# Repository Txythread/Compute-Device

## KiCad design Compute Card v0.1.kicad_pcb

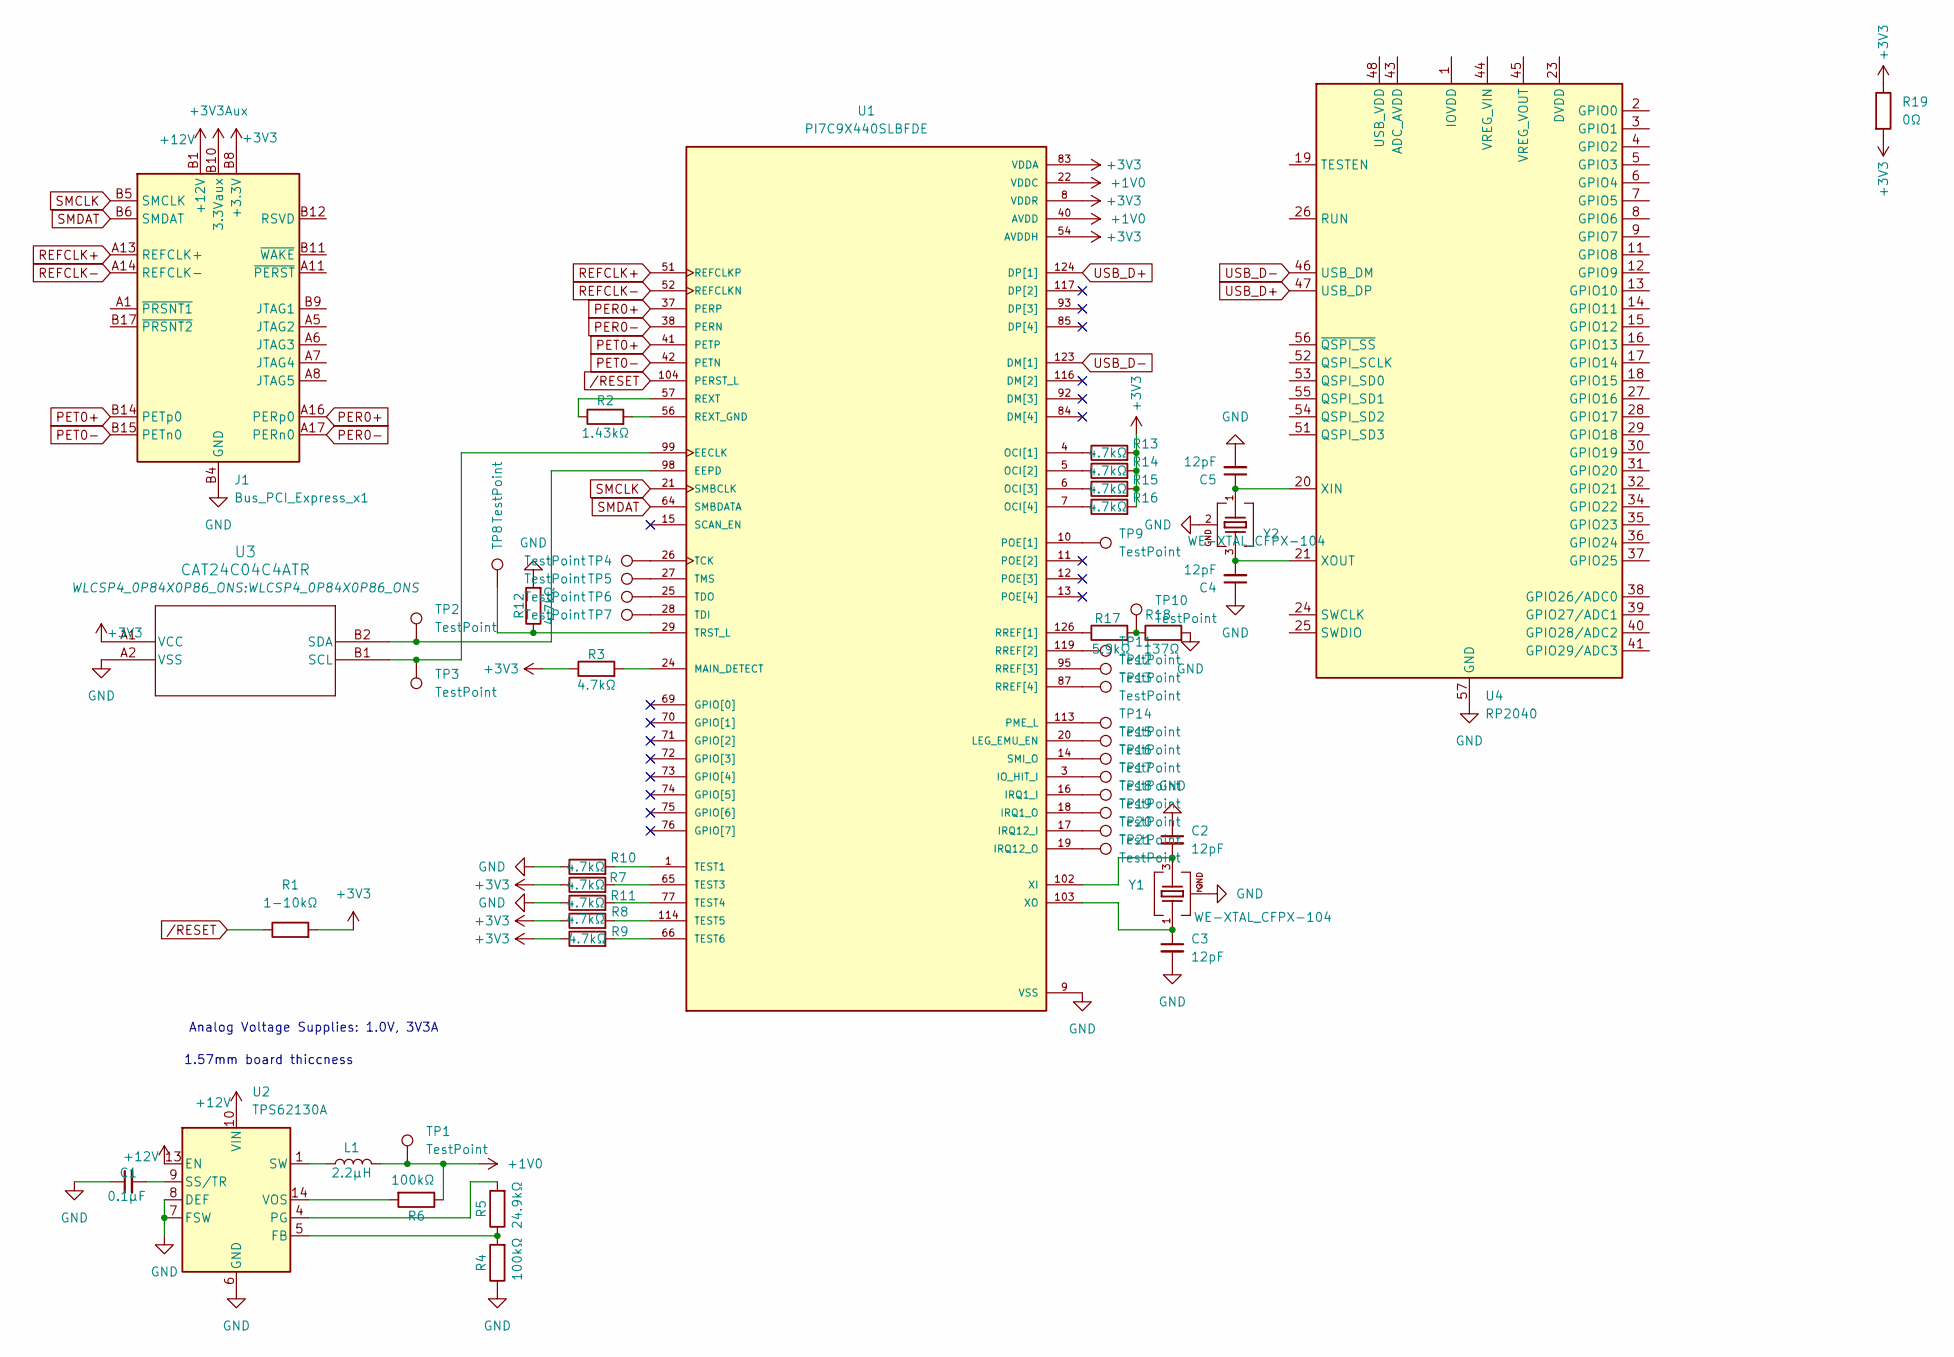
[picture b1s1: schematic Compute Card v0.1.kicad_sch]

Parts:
C1: 0.1µF; C_0805_2012Metric_Pad1.18x1.45mm_HandSolder
C2, C3, C4, C5: 12pF; C_0603_1608Metric
J1: Bus_PCI_Express_x1; BUS_PCIexpress_x1
L1: 2.2µH; L_0805_2012Metric_Pad1.05x1.20mm_HandSolder
R1: 1-10kΩ; R_0603_1608Metric_Pad0.98x0.95mm_HandSolder
R2: 1.43kΩ; R_0603_1608Metric_Pad0.98x0.95mm_HandSolder
R3, R7, R8, R9, R10, R11, R12, R13, R14, R15, R16: 4.7kΩ; R_0805_2012Metric_Pad1.20x1.40mm_HandSolder
R4, R6: 100kΩ; R_0805_2012Metric_Pad1.20x1.40mm_HandSolder
R5: 24.9kΩ; R_0805_2012Metric_Pad1.20x1.40mm_HandSolder
R17: 5.9kΩ; R_0603_1608Metric
R18: 137Ω; R_1206_3216Metric
R19: 0Ω; R_0805_2012Metric
TP1, TP2, TP3, TP4, TP5, TP6, TP7, TP8, TP9, TP10, TP11, TP12, TP13, TP14, TP15, TP16, TP17, TP18, TP19, TP20, TP21: TestPoint; TestPoint_Pad_D1.0mm
U1: PI7C9X440SLBFDE; QFP40P1600X1600X160-129N; PARTREV 3; DigiKey_Part_Number PI7C9X440SLBFDE-ND
U2: TPS62130A; VQFN-16-1EP_3x3mm_P0.5mm_EP1.68x1.68mm_ThermalVias
U3: CAT24C04C4ATR; WLCSP4_0P84X0P86_ONS
U4: RP2040; QFN-56-1EP_7x7mm_P0.4mm_EP3.2x3.2mm_ThermalVias
Y1, Y2: WE-XTAL_CFPX-104; DigiKey_Part_Number 1923-830059522CT-ND

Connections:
+1V0: L1.2, R6.1, TP1.1, U1.22 (VDDC), U1.35 (VDDC), U1.40 (AVDD), U1.46 (AVDD), U1.49 (AVDD), U1.60 (AVDD), U1.81 (VDDC), U1.100 (VDDC), U1.109 (VDDC), U1.111 (VDDC)
+3V3: J1.A9 (+3.3V), J1.A10 (+3.3V), J1.B8 (+3.3V), R1.2, R3.1, R7.1, R8.1, R9.1, R13.2, R14.2, R15.2, R16.2, R19.1, R19.2, U1.8 (VDDR), U1.33 (VDDR), U1.54 (AVDDH), U1.67 (VDDR), U1.83 (VDDA), U1.90 (VDDA), U1.91 (VDDA), U1.97 (VDDA), U1.105 (VDDR), U1.112 (VDDR), U1.115 (VDDA), U1.121 (VDDA), U1.122 (VDDA), U1.128 (VDDA), U3.A1 (VCC)
+3V3Aux: J1.B10 (3.3Vaux)
+12V: J1.A2 (+12V), J1.A3 (+12V), J1.B1 (+12V), J1.B2 (+12V), J1.B3 (+12V), U2.10 (VIN), U2.11 (VIN), U2.12 (VIN), U2.13 (EN)
GND: C1.1, C2.1, C3.2, C4.1, C5.2, J1.A4 (GND), J1.A12 (GND), J1.A15 (GND), J1.A18 (GND), J1.B4 (GND), J1.B7 (GND), J1.B13 (GND), J1.B16 (GND), J1.B18 (GND), R4.1, R10.1, R11.1, R12.2, R18.2, U1.9 (VSS), U1.23 (VSS), U1.34 (VSS), U1.36 (VSS), U1.39 (VSS), U1.45 (VSS), U1.50 (VSS), U1.53 (VSS), U1.61 (VSS), U1.68 (VSS), U1.82 (VSS), U1.86 (VSS), U1.89 (VSS), U1.94 (VSS), U1.96 (VSS), U1.101 (VSS), U1.106 (VSS), U1.110 (VSS), U1.118 (VSS), U1.120 (VSS), U1.125 (VSS), U1.127 (VSS), U1.129 (VSS), U2.6 (GND), U2.7 (FSW), U2.8 (DEF), U2.15 (GND), U2.16 (GND), U2.17 (GND), U3.A2 (VSS), U4.57 (GND), Y1.2, Y1.4, Y2.2, Y2.4
unnamed: L1.1, U2.1 (SW), U2.2 (SW), U2.3 (SW)
unnamed: R17.2, R18.1, TP10.1
unnamed: TP3.1, U1.99 (EECLK), U3.B1 (SCL)
unnamed: TP2.1, U1.98 (EEPD), U3.B2 (SDA)
unnamed: TP17.1, U1.3 (IO_HIT_I)
unnamed: TP18.1, U1.16 (IRQ1_I)
unnamed: TP19.1, U1.18 (IRQ1_O)
unnamed: TP20.1, U1.17 (IRQ12_I)
unnamed: TP21.1, U1.19 (IRQ12_O)
unnamed: TP15.1, U1.20 (LEG_EMU_EN)
unnamed: R3.2, U1.24 (MAIN_DETECT)
unnamed: R13.1, U1.4 (OCI[1])
unnamed: R14.1, U1.5 (OCI[2])
unnamed: R15.1, U1.6 (OCI[3])
unnamed: R16.1, U1.7 (OCI[4])
unnamed: TP14.1, U1.113 (PME_L)
unnamed: TP9.1, U1.10 (POE[1])
unnamed: R2.1, U1.57 (REXT)
unnamed: R2.2, U1.56 (REXT_GND)
unnamed: R17.1, U1.126 (RREF[1])
unnamed: TP11.1, U1.119 (RREF[2])
unnamed: TP12.1, U1.95 (RREF[3])
unnamed: TP13.1, U1.87 (RREF[4])
unnamed: TP16.1, U1.14 (SMI_O)
unnamed: TP4.1, U1.26 (TCK)
unnamed: TP7.1, U1.28 (TDI)
unnamed: TP6.1, U1.25 (TDO)
unnamed: R10.2, U1.1 (TEST1)
unnamed: R7.2, U1.65 (TEST3)
unnamed: R11.2, U1.77 (TEST4)
unnamed: R8.2, U1.114 (TEST5)
unnamed: R9.2, U1.66 (TEST6)
unnamed: TP5.1, U1.27 (TMS)
unnamed: R12.1, TP8.1, U1.29 (TRST_L)
unnamed: C2.2, U1.102 (XI), Y1.3
unnamed: C3.1, U1.103 (XO), Y1.1
unnamed: R4.2, R5.1, U2.5 (FB)
unnamed: R5.2, U2.4 (PG)
unnamed: C1.2, U2.9 (SS/TR)
unnamed: R6.2, U2.14 (VOS)
unnamed: U4.23 (DVDD), U4.50 (DVDD)
unnamed: U4.1 (IOVDD), U4.10 (IOVDD), U4.22 (IOVDD), U4.33 (IOVDD), U4.42 (IOVDD), U4.49 (IOVDD)
unnamed: C5.1, U4.20 (XIN), Y2.1
unnamed: C4.2, U4.21 (XOUT), Y2.3
PER0+: J1.A16 (PERp0), U1.37 (PERP)
PER0-: J1.A17 (PERn0), U1.38 (PERN)
PET0+: J1.B14 (PETp0), U1.41 (PETP)
PET0-: J1.B15 (PETn0), U1.42 (PETN)
REFCLK+: J1.A13 (REFCLK+), U1.51 (REFCLKP)
REFCLK-: J1.A14 (REFCLK-), U1.52 (REFCLKN)
SMCLK: J1.B5 (SMCLK), U1.21 (SMBCLK)
SMDAT: J1.B6 (SMDAT), U1.64 (SMBDATA)
USB_D+: U1.124 (DP[1]), U4.47 (USB_DP)
USB_D-: U1.123 (DM[1]), U4.46 (USB_DM)
/RESET: R1.1, U1.104 (PERST_L)

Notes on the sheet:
1.57mm board thiccness
Analog Voltage Supplies: 1.0V, 3V3A

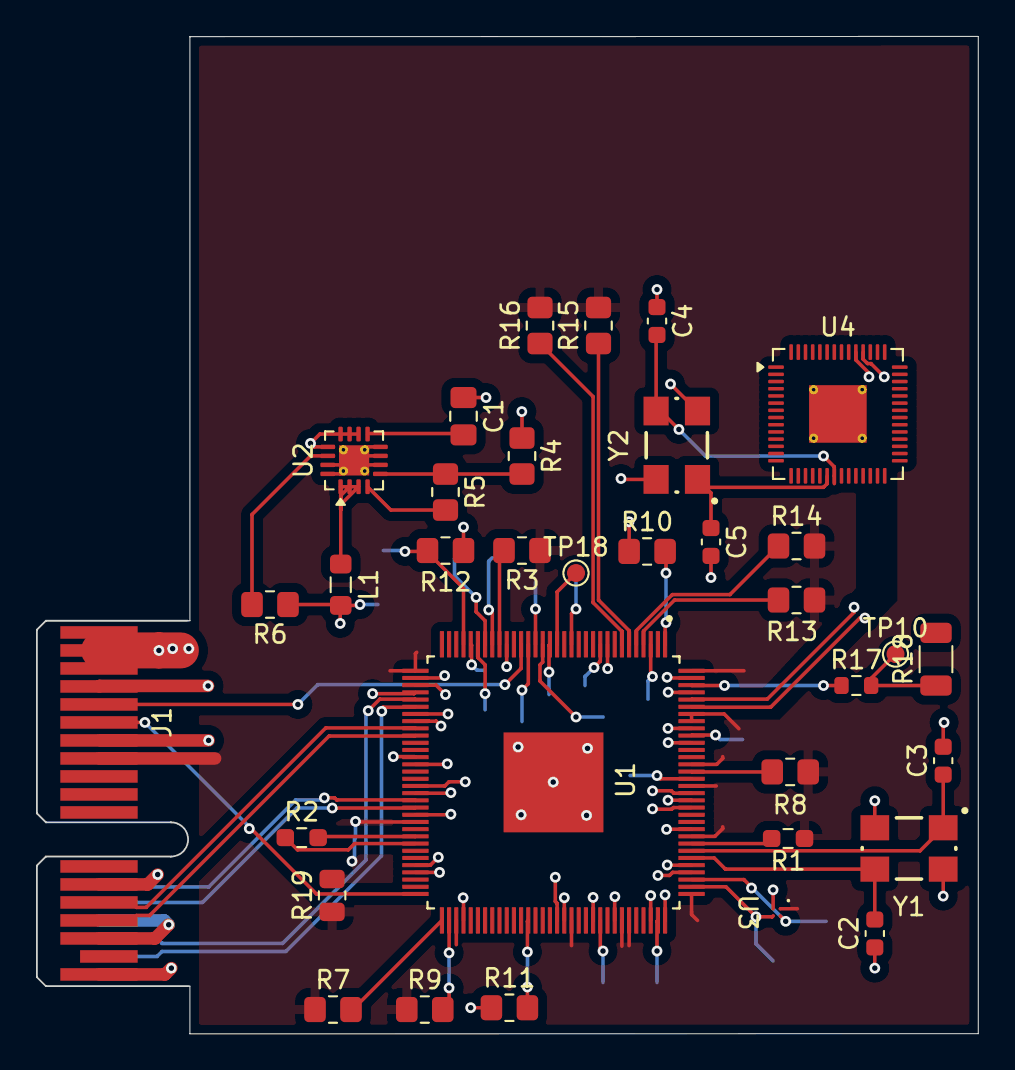
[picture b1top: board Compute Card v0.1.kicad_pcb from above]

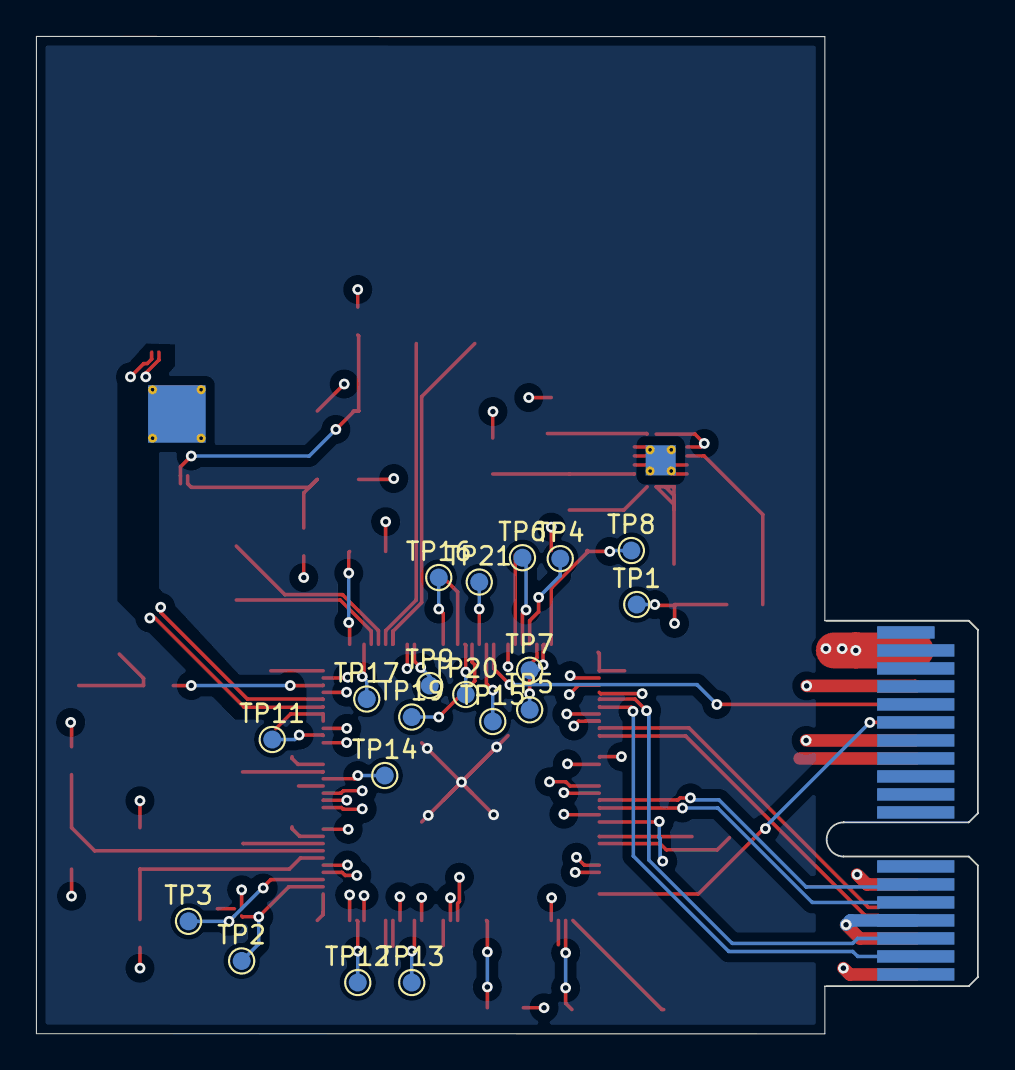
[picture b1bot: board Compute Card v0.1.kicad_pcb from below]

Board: 4 copper layers, 52.3 x 55.4 mm, 53 parts (19 on the bottom side), 59 nets.

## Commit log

2026-02-06 Created Zones, Found Useful Chips
2026-02-07 Added Schematic for 1V0
2026-02-07 Added .gitignore
2026-02-07 Placed 1V0 parts
2026-02-08 Almost Completed PCIe Interface
2026-02-08 Added RP2ß40 as Main MCU
2026-02-08 Completed PCIe to USB Bridge
